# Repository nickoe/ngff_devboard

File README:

This is a project to make "something" to put in the WWAN slot of my
laptop. This means M.2 NGFF with key B. Lets try to use USB as a
minimum. Maybe som STM32 chip as a start. Maybe it can be connected to
other things. This in turn means a maximum component area of 30mm x
42mm. Meaning TYPE 3042-xx-B. But I gues we could also go with TYPE
2242-xx-B-M, but this is smaller, but should fit a normal WWAN socket
location as well.

[AetherJack](misc/mostly_top_raytracing_no_socket.png)

Or A + E?  Can we do A + B + E?

Even though there are USB in all of above the USB data lines are NOT
in the same pin location :( ... meaning that we go with the B key for
now as this seems to be the most common keying for WWAN modules for
laptops.

Mechanical constraints:
 - Type 3042-S3-B interface
   - 30x42mm
   - Component maximum height on top layer is 1.5mm
   - B keying
   - Board thickness is 0.8 mm.
   - No components on bottom side

   --- or should it be 2242-S3-B? 22mm instead of 30mm wide?
   - Refer to Table 30 for pinout
      Socket 2 Key B SSIC-based WWAN Adapter Pinouts

SIM card connections could be used for SWD programming
Make PCB ready for both STM32F407 and STM32F103

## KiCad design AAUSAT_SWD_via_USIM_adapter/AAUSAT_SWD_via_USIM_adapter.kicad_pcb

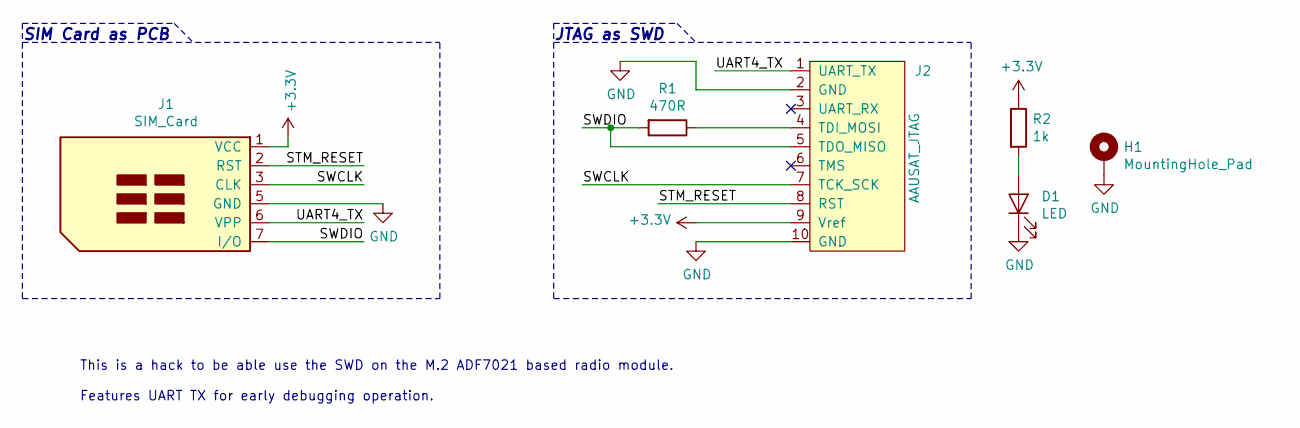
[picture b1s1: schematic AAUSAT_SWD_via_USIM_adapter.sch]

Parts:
D1: LED; LED_0603_1608Metric
H1: MountingHole_Pad; MountingHole_3.2mm_M3_Pad
J1: SIM_Card; UICC_2FF_mini_SIM_6_pads
J2: AAUSAT_JTAG; S10B-ZR-SM4A-TF(LF)(SN); digikey# 455-1700-1-ND;455-1197-ND;10:455-1130-1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
R1: 470R; R_0603_1608Metric
R2: 1k; R_0603_1608Metric

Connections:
+3V3: J1.1 (VCC), J2.9 (Vref), R2.1
/STM_RESET: J1.2 (RST), J2.8 (RST)
/SWCLK: J1.3 (CLK), J2.7 (TCK_SCK)
/SWDIO: J1.7 (I/O), J2.5 (TDO_MISO), R1.2
/UART4_TX: J1.6 (VPP), J2.1 (UART_TX)
GND: D1.1 (K), H1.1, J1.5 (GND), J2.2 (GND), J2.10 (GND)
unnamed: D1.2 (A), R2.2
unnamed: J2.4 (TDI_MOSI), R1.1

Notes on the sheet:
JTAG as SWD
SIM Card as PCB
This is a hack to be able use the SWD on the M.2 ADF7021 based radio module. Features UART TX for early debugging operation.

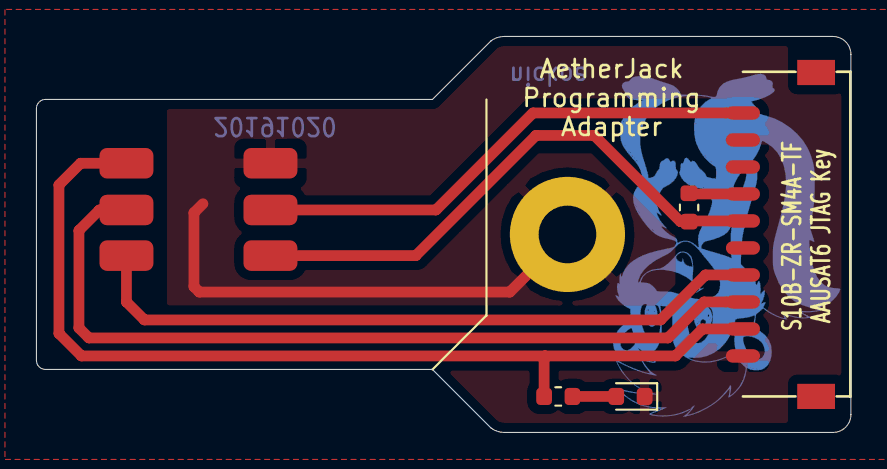
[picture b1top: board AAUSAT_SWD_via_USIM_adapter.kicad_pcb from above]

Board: 2 copper layers, 45.2 x 22.0 mm, 6 parts (0 on the bottom side), 8 nets.

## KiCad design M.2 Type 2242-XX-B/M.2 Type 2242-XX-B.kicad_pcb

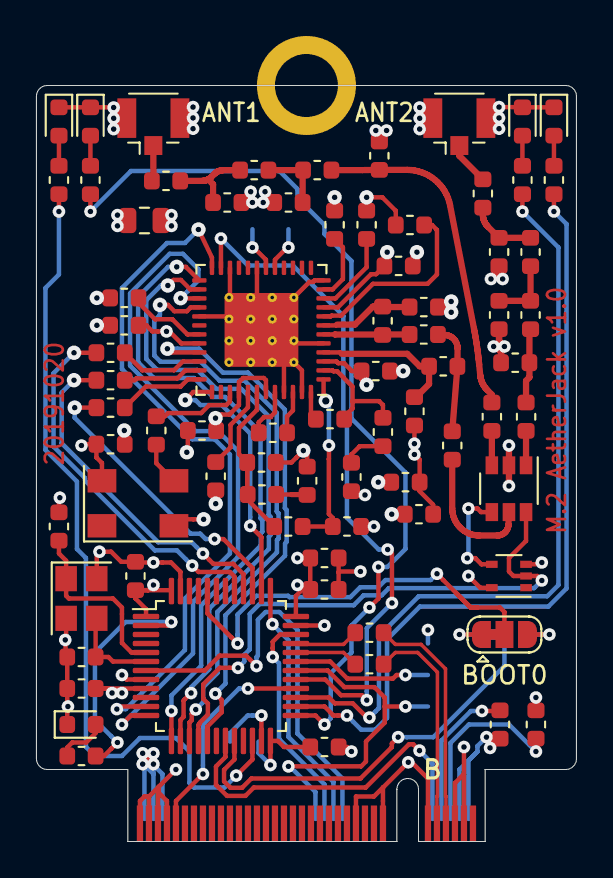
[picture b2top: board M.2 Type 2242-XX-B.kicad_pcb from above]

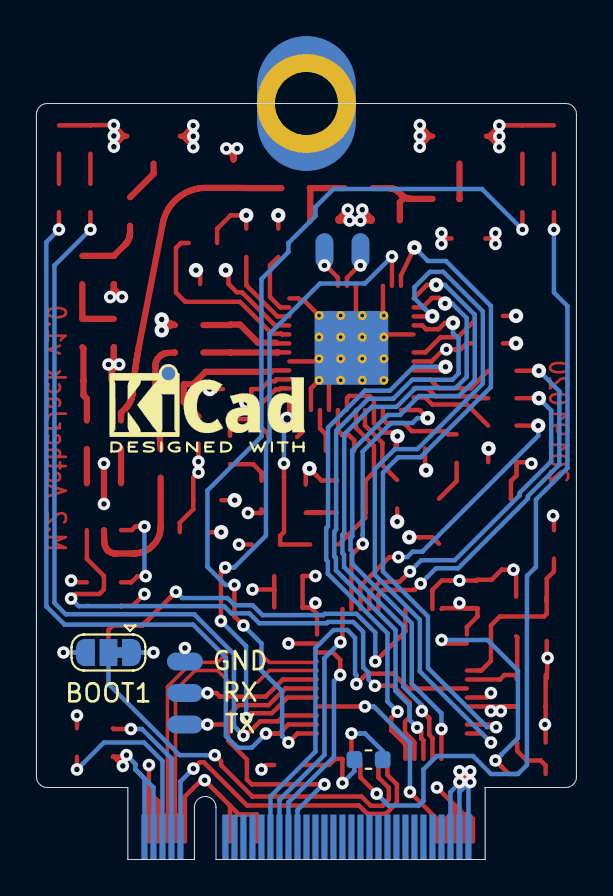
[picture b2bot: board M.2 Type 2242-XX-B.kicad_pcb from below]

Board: 4 copper layers, 30.0 x 42.0 mm, 86 parts (8 on the bottom side), 77 nets.

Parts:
C201, C202: 27pF; C_0603_1608Metric
C203, C204, C205, C206, C207, C208: 100n; C_0603_1608Metric
C401: 10uF; C_0805_2012Metric
C402, C403, C406: 100pF; C_0603_1608Metric
C404, C407, C427, C429: C; C_0603_1608Metric
C405, C428: 6.8pF; C_0603_1608Metric
C408, C414, C415, C422, C425, C426: 10nF; C_0603_1608Metric
C409, C411, C412: 11pF; C_0603_1608Metric
C410: 220pF; C_0603_1608Metric
C413, C416, C423, C424: 100nF; C_0603_1608Metric
C417: 470pF; C_0603_1608Metric
C418: 22nF; C_0603_1608Metric
C419: 15nF; C_0603_1608Metric
C420: 1nF; C_0603_1608Metric
C421: 22pF; C_0603_1608Metric
D201: LED_A_TX; LED_0603_1608Metric
D202: LED0; LED_0603_1608Metric
D203: LED_A_RX; LED_0603_1608Metric
D204: LED_B_TX; LED_0603_1608Metric
D205: LED_B_RX; LED_0603_1608Metric
J101: ANT1; U.FL_Hirose_U.FL-R-SMT-1_Vertical
J102: ANT2; U.FL_Hirose_U.FL-R-SMT-1_Vertical
L401, L407: 0R; L_0603_1608Metric
L402, L408: 22nH; L_0603_1608Metric
L403, L409: 20nH; L_0603_1608Metric
L404: 180nH; L_0603_1608Metric
L405: 68nH; L_0603_1608Metric
L406: 17nH; L_0603_1608Metric
LOGO401: TestPoint_Alt_Short; KiCad-Logo_Back
M201: MountingHole_Pad; M.2_Standoff_Card_Pad
R201, R202: 20R; R_0603_1608Metric
R203, R204, R205, R206, R207: 10K; R_0603_1608Metric
R301, R302: 200K; R_0603_1608Metric
R401: 1K1; R_0603_1608Metric
R402: 3R9; R_0603_1608Metric
R403: 3K6; R_0603_1608Metric
R404: 560R; R_0603_1608Metric
R405: 270R; R_0603_1608Metric
R406, R407, R408: 1K; R_0603_1608Metric
SJ201: BOOT0; SolderJumper-3_P1.3mm_Bridged12_RoundedPad1.0x1.5mm
SJ202: BOOT1; SolderJumper-3_P1.3mm_Bridged12_RoundedPad1.0x1.5mm
TP201: TX; TestPad
TP202: RX; TestPad
TP203: GND; TestPad
TP401: FILT_I; TestPad
TP402: ~FILT_I; TestPad
U201: STM32F103C8Tx; LQFP-48_7x7mm_P0.5mm
U301: M.2_NGFF_Socket2_KeyB_SSIC_Adapter; M.2_Key_B_Fingers
U401: AS193-73; SuperSOT-6
U402: M74VHC1GT04DFT1G; SOT-353_SC-70-5
U403: ADF7021BCPZ; LFCSP-48-1EP_7x7mm_P0.5mm_EP4.1x4.1mm_ThermalVias
X401: FT5HNBPK19.44-T1; FOX924
Y201: 12MHz; Crystal_SMD_3225-4Pin_3.2x2.5mm

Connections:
+3V3: C203.1, C204.1, C205.1, C206.1, C207.1, C208.1, C401.1, C408.1, C410.1, C414.1, C415.1, C422.1, C425.1, C426.1, L405.1, R301.1, SJ201.3, SJ202.3, U201.1, U201.9, U201.24, U201.36, U201.48, U301.2, U301.4, U301.70, U301.72, U301.74, U402.5, U403.3, U403.9, U403.32, U403.40, U403.43, X401.4
/M.2 NGFF Fingers/RESET#: U201.28, U301.67
/M.2 NGFF Fingers/USB_D+: R201.2, U301.7
/M.2 NGFF Fingers/USB_D-: R202.2, U301.9
/Microcontroller/ADF1_ANT_SELECT: U201.16, U401.6, U402.2
/Microcontroller/ADF1_CE: U201.11, U403.24
/Microcontroller/ADF1_MUXOUT: U201.38, U403.37
/Microcontroller/ADF1_SCLK: U201.15, U403.28
/Microcontroller/ADF1_SDATA: U201.14, U403.26
/Microcontroller/ADF1_SLE: U201.13, U403.25
/Microcontroller/ADF1_SREAD: U201.12, U403.27
/Microcontroller/ADF1_SWD: U201.17, U403.33
/Microcontroller/ADF1_TEST_A: U201.29, U403.23
/Microcontroller/BOOT0: SJ201.2, U201.44
/Microcontroller/BOOT1: SJ202.2, U201.20
/Microcontroller/LED0: R204.1, U201.2
/Microcontroller/LED1: U201.19, U301.10
/Microcontroller/LED_A_RX: R205.1, U201.25
/Microcontroller/LED_A_TX: R203.1, U201.22
/Microcontroller/LED_B_RX: R207.1, U201.27
/Microcontroller/LED_B_TX: R206.1, U201.26
/Microcontroller/STM_RESET: U201.7, U301.30
/Microcontroller/SWCLK: U201.37, U301.32
/Microcontroller/SWDIO: U201.34, U301.34
/Microcontroller/UART1_RX: TP202.1, U201.31
/Microcontroller/UART_TX: TP201.1, U201.30, U301.36
/Microcontroller/USB_OTG_FS_D+: R201.1, U201.33
/Microcontroller/USB_OTG_FS_D-: R202.1, U201.32
/Radio Tranceiver/ADF_CLKOUT: R408.1, U201.39
/Radio Tranceiver/ADF_DATA_CLK: R407.1, U201.40
/Radio Tranceiver/ADF_DATA_IO: R406.1, U201.41
/Radio Tranceiver/ANT_A: J101.1, L407.1
/Radio Tranceiver/ANT_B: J102.1, L401.1
/Radio Tranceiver/RF_A: C403.2, C429.1, L409.2
/Radio Tranceiver/RF_B: C402.2, C407.1, L403.2
/Radio Tranceiver/RF_RXTX: C406.1, C409.1, C412.1
GND: C201.2, C202.2, C203.2, C204.2, C205.2, C206.2, C207.2, C208.2, C401.2, C404.2, C405.2, C407.2, C408.2, C410.2, C411.2, C413.2, C414.2, C415.2, C416.2, C417.2, C419.2, C420.2, C422.2, C423.2, C424.2, C425.2, C426.2, C427.2, C428.2, C429.2, D201.1, D202.1, D203.1, D204.1, D205.1, J101.2, J102.2, M201.1, R302.2, R401.2, R403.2, SJ201.1, SJ202.1, TP203.1, U201.8, U201.23, U201.35, U201.47, U301.3, U301.5, U301.11, U301.21, U301.27, U301.69, U301.71, U301.73, U301.75, U401.2, U402.3, U403.5, U403.12, U403.19, U403.22, U403.29, U403.45, U403.47, U403.49, X401.2, Y201.2, Y201.4
unnamed: C201.1, U201.5, Y201.1
unnamed: C202.1, U201.6, Y201.3
unnamed: C402.1, U401.1
unnamed: C403.1, U401.3
unnamed: C404.1, L401.2, L402.1
unnamed: C405.1, L402.2, L403.1
unnamed: C406.2, U401.5
unnamed: C409.2, L404.1, U403.6
unnamed: C411.1, L404.2, U403.7
unnamed: C412.2, L405.2, U403.4
unnamed: C413.1, R402.2
unnamed: C416.1, U403.11
unnamed: C417.1, R404.2, U403.1
unnamed: C418.1, U403.48
unnamed: C418.2, R402.1, U403.2
unnamed: C419.1, R405.2
unnamed: C420.1, R404.1, R405.1, U403.42
unnamed: C421.1, X401.3
unnamed: C421.2, U403.39
unnamed: C423.1, U403.41
unnamed: C424.1, U403.31
unnamed: C427.1, L407.2, L408.1
unnamed: C428.1, L408.2, L409.1
unnamed: D201.2, R203.2
unnamed: D202.2, R204.2
unnamed: D203.2, R205.2
unnamed: D204.2, R206.2
unnamed: D205.2, R207.2
unnamed: L406.1, U403.46
unnamed: L406.2, U403.44
unnamed: R301.2, U301.8
unnamed: R302.1, U301.6
unnamed: R401.1, U403.8
unnamed: R403.1, U403.10
unnamed: R406.2, U403.34
unnamed: R407.2, U403.35
unnamed: R408.2, U403.36
unnamed: TP401.1, U403.17
unnamed: TP402.1, U403.18
unnamed: U401.4, U402.4

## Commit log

2019-10-13 Add gitignore for kicad files
2019-10-13 Add initial schematic for M.2 board
2019-10-13 Add SWD via SIM card adapter
2019-10-13 Add proper footprint to solder jumpers
2019-10-14 NOP Update
2019-10-14 Initial placement, I think we are going for the STM32F103 instead
    The LQPF-100 is simply too big
2019-10-14 Schematic updated to STM32F103
2019-10-14 Almost everything placed
2019-10-14 Remove the solder pads for the config pins
    Lets hope it is working as is. The board does not really have a lot of
    real estate left...
2019-10-15 Fix 3D model path for M.2 connector
2019-10-15 Board more or less completely routed
2019-10-16 Add datasheets
2019-10-16 Update clearance rules for M.2 fingers
2019-10-16 Add project named, data and antenna numbers
2019-10-18 Shorten adapter, it was a bit too long
2019-10-19 Add rounded corners
2019-10-19 Add image for preview
2019-10-19 Add image
2019-10-19 Make README be parsed as md
2019-10-19 Fix image link
2019-10-20 Fix DRC error with ANT1/2 in copper
    Add solder mask removal for RF traces
2019-10-20 Add skunk and name of board
2019-10-20 Adjust my nickname
2019-10-20 Add date on adapter
2019-10-21 Backlink to CADLAB.io has been added.
